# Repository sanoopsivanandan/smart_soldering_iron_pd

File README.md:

# Smart Soldering Iron (USB-C PD Powered)

A compact and affordable **USB-C PD powered smart soldering iron** designed for hobbyists and experimenters.
The project uses a **C210-style tip**, an **ATmega328P-AU**, and includes an **OLED display** and **accelerometer** for smart functions.

This repository currently contains **hardware-only KiCad files**. Firmware development will begin later.

---

## 📏 PCB Specifications

* **Size:** 15 mm × 107 mm
* **Layers:** 2-layer PCB
* **Form factor:** Ultra-slim to fit inside a pen-style soldering iron handle
* **Designed for:** C210-style soldering tip

---

## 🔌 Power System

* **Input:** USB-C Power Delivery
* **Supported Voltage:** Up to **12V** (currently limited to 12V for testing)
* **Purpose:** Drive the heater inside the C210 tip and power the MCU + peripherals

---

## 🧠 Microcontroller

* **MCU:** ATmega328P-AU
* **Package:** TQFP-32 (same package used in Arduino Uno SMD version)
* **Reason:** Easy programming, hobbyist-friendly, widely supported by Arduino IDE

---

## 🔥 Soldering Tip Support

* **Tip Type:** C210 series
* **Temperature Sensor:** Built-in thermocouple inside the tip
* **Connection:** Compact, high-current heater + thermocouple feedback

---

## 📟 Display & User Interface

* **Display:** 128×32 OLED
* **Navigation:** Buttons + planned touch navigation for PDF schematic viewing
* **Future UI Features:**

  * Temperature selection menu
  * Left-hand / right-hand screen rotation
  * Real-time tip temperature graph (optional)

---

## 🧭 Motion / Sleep Features

* **Accelerometer:** LIS3DHTR
* Planned features:

  * Auto-sleep when inactive
  * Wake-on-shake
  * Handle movement detection for safety

---

## 🧪 Project Status

| Category   | Status                        |
| ---------- | ----------------------------- |
| Hardware   | ✔ Completed (prototype ready) |
| Schematics | ✔ Completed                   |
| PCB Layout | ✔ Completed                   |
| Firmware   | ❌ Not started                 |
| Testing    | ❌ Pending                     |

---

## 🧰 Development Plans (Firmware)

Firmware will be written primarily using **Arduino IDE**, with possible low-level C enhancements.

Planned firmware features:

* PID temperature control
* USB-C PD negotiation and power step handling
* On-screen temperature display
* Menu navigation
* Accelerometer-based sleep mode
* Tip calibration

---

## 📂 Repository Structure

* `.kicad_pro` – Main KiCad project file
* `.kicad_sch` – Schematic files
* `.kicad_pcb` – PCB layout
* `pcb_front.pdf` / `pcb_back.pdf` – PDF views of the PCB
* Additional supporting schematic sheets

Touch navigation support will be added to PDF schematics to improve readability during review.

---

## 🎯 Project Goal

To create an **affordable**, **compact**, and **easily buildable** smart soldering iron that:

* Hobbyists can assemble with basic tools
* Works reliably with USB-C PD chargers
* Uses a high-quality C210 tip
* Provides a solid foundation for firmware experimentation

---

## 📜 License

No license added yet — you may add MIT / GPL / CERN OHL based on your preference.

---

## 🤝 Contributions

Contributions and suggestions are welcome once firmware development begins!

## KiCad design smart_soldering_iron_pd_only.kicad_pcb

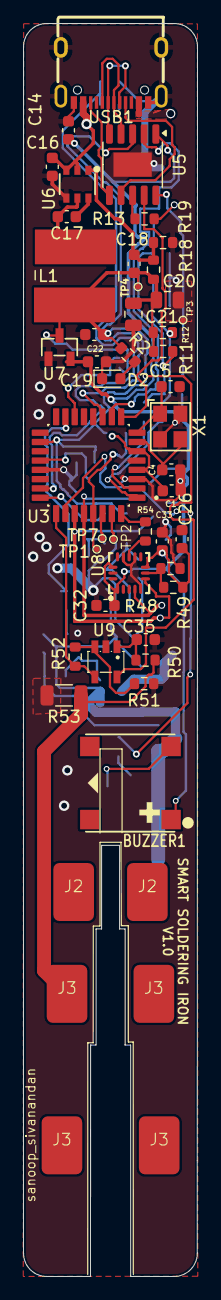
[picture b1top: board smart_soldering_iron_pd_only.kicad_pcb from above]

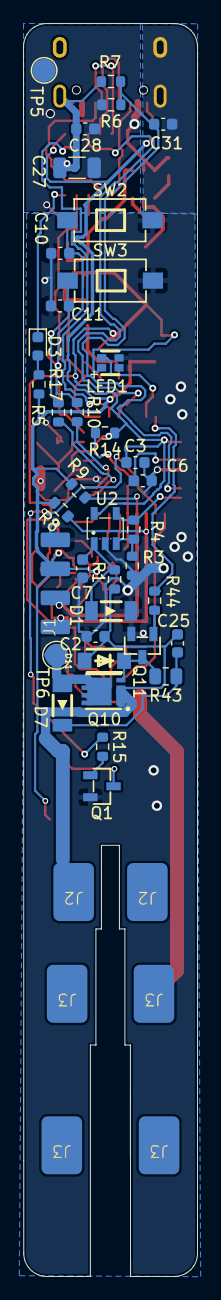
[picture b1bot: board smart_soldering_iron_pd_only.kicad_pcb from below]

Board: 2 copper layers, 15.0 x 107.9 mm, 94 parts (44 on the bottom side), 51 nets.

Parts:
BUZZER1: 2.7kHz; BUZZER_7525A_BUZ-SMD_4P-L7.5-W7.5-P7.59-TL
C1, C3, C6, C10, C11, C17, C26, C31, C32, C35: 100n; C_0603_1608Metric
C2: 1u 35V; C_0603_1608Metric
C4, C5: 22P; C_0603_1608Metric
C7: 2n2; C_0603_1608Metric
C14, C19, C22: 1u; C_0603_1608Metric
C16, C25, C33: 10u; C_0603_1608Metric
C18: 47p; C_0603_1608Metric
C20, C21: 22u; C_0805_2012Metric
C27: 100u 35V; C_1206_3216Metric
C28: 10u 35V; C_0603_1608Metric
D1, D7: D; LL4148 LL34 SOD80 1N4148 Hottech SMD diode
D2, D3: LED; LED_0603_1608Metric
D11: D_Zener; BZT52C5V1 W8_ZENER DIODE
J1: Conn_01x04_Pin; oled_display
J2, J2#2, J2#3, J2#4: TIP_SMALL_END; TIP_PADS
J3, J3#2, J3#3, J3#4, J3#5, J3#6, J3#7, J3#8: TIP_MID; TIP_PADS
L1: 4.7u; L_Wuerth_WE-PD2-Typ-L
LED1: LED-SMD_4P-L1.6-W1.5_XL-1615RGBC-WS2812B-S
Q1, Q11: S8050_TRANSIS_25V_0.5A_npn_SOT-23-3_L2.9-W1.3-P1.90-LS2.4-BR
Q10: AON7410_POWER_N_MOS_DFN-8_L3.0-W3.0-P0.65-BL
R1, R7, R8, R9, R11, R12, R13, R14, R15, R44, R48, R49: 10K; R_0603_1608Metric
R2, R3, R51, R54: 1K; R_0603_1608Metric
R4: 200K; R_0603_1608Metric
R5, R10: 0; R_0603_1608Metric
R6: 33K; R_0603_1608Metric
R17: 470; R_0603_1608Metric
R18: 9K; R_0603_1608Metric
R19: 30K; R_0603_1608Metric
R43: 1K; R_0805_2012Metric
R50: 56K; R_0603_1608Metric
R52: 75K; R_0603_1608Metric
R53: 0.01; R_1206_3216Metric
SW2, SW3: push_button_3.5x6x2.5Hmm SMD Rectangle Tactile micro Switch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
TP1, TP2, TP3, TP4, TP7: TestPoint; TestPoint_Pad_D1.5mm
TP5, TP6: TestPoint; TestPoint_Pad_D2.0mm
U2, U9: LM321_SOT-23-5_L3.0-W1.7-P0.95-LS2.8-BR
U3: ATMEGA328P-AU; ATMEGA328P-AU_QFP80P900X900X120-32N
U5: CH224K; SSOP-10-1EP_3.9x4.9mm_P1mm_EP2.1x3.3mm
U6: DIODES AP63300WU-7_buck_TSOT-23-6_L2.9-W1.6-P0.95-LS2.8-BR
U7: XC6206P332MR_SOT-23-3_L2.9-W1.3-P1.90-LS2.4-BR
U8: ST LIS3DHTR_ACCELEROMETER_LGA-16_L3.0-W3.0-P0.50-TL
USB1: USB-C-SMD_TYPE-C-6PIN-2MD-073
X1: 16MHz; 16_mhz_OSC-SMD_4P-L3.2-W2.5-BL

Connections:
<_BUTTON: R10.2, U3.2 (PD4)
>_BUTTON: R5.2, U3.1 (PD3)
AREF: C6.1, U3.20 (AREF)
BUZZER: R15.1, U3.26 (PC3)
CFG1: U3.9 (PD5), U5.9 (CFG1)
CFG2: U3.10 (PD6), U5.2 (CFG2)
CFG3: U3.11 (PD7), U5.3 (CFG3)
D0_RXD: TP1.1, U3.30 (PD0)
D1_TXD: TP2.1, U3.31 (PD1)
GND: C1.2, C2.2, C3.2, C4.2, C5.2, C6.2, C7.2, C10.1, C11.1, C14.2, C16.2, C19.2, C20.2, C21.2, C22.2, C26.1, C27.2, C28.2, C31.2, C32.1, C33.1, C35.2, D1.1 (K), D2.1 (K), J1.4, LED1.3 (GND), Q1.2 (E), Q11.2 (E), R3.1, R7.1, R19.2, R49.1, R51.1, R53.2, SW2.2, SW3.2, TP3.1, U2.2 (V-), U3.3 (GND), U3.5 (GND), U3.21 (GND), U5.11 (GND), U6.4 (GND), U7.1 (VSS), U8.5 (GND), U8.10 (RES), U8.12 (GND), U9.2 (V-), USB1.1 (GND), USB1.12 (GND), USB1.13 (SHELL), USB1.14 (SHELL), X1.2 (GND), X1.4 (GND)
LED_RGB: LED1.4 (DI), U3.14 (PB2)
LIS3DHTR_INT: R54.1, U3.32 (PD2)
unnamed: BUZZER1.2 (-), Q1.3 (C)
unnamed: C10.2, R10.1, R11.1, SW2.1
unnamed: C11.2, R5.1, R12.1, SW3.1
unnamed: C7.1, D1.2 (A), R1.2, U2.1 (IN+)
unnamed: D2.2 (A), R2.2
unnamed: D3.2 (A), R17.1
unnamed: D7.2 (A), Q10.5 (D), Q10.6 (D), Q10.7 (D), Q10.8 (D), Q10.9 (D), TP6.1
unnamed: C25.2, D7.1 (K), R43.1
unnamed: D11.1 (K), Q10.4 (G), Q11.3 (C), R43.2
unnamed: Q1.1 (B), R15.2
unnamed: Q11.1 (B), R44.2
unnamed: R3.2, R4.1, U2.3 (IN-)
unnamed: R14.2, TP7.1, U3.29 (PC6/~RESET)
unnamed: U5.7 (CC1), USB1.4 (CC1)
unnamed: U5.6 (CC2), USB1.10 (CC2)
unnamed: U5.5 (DM), USB1.5 (DN2), USB1.7 (DN1)
unnamed: U5.4 (DP), USB1.6 (DP1), USB1.8 (DP2)
unnamed: R13.2, U5.8 (VBUS)
unnamed: C17.1, U6.6 (BST)
unnamed: C18.2, R18.2, R19.1, U6.1 (FB)
unnamed: C17.2, L1.1, U6.5 (SW)
unnamed: R54.2, U8.11 (INT1)
unnamed: R48.1, R49.2, U8.7 (SDO/SA0)
unnamed: C35.1, R50.2, U9.1 (IN+)
unnamed: R51.2, R52.1, U9.3 (IN-)
PG: D3.1 (K), U5.10 (PG)
SCL: J1.2, R9.1, U3.28 (PC5), U8.4 (SCL/SPC)
SDA: J1.1, R8.1, U3.27 (PC4), U8.6 (SDA/SDI/SDO)
TEMP_SENSE: R4.2, U2.4 (OUT), U3.24 (PC1)
TIP+: C2.1, C25.1, D11.2 (A), J2#3.1, Q10.1 (S), Q10.2 (S), Q10.3 (S), R1.1
TIP-: J3#3.1, R50.1, R53.1
TIP_AMP_SENSE: R52.2, U3.25 (PC2), U9.4 (OUT)
TIP_MOS: R44.1, U3.15 (PB3)
VCC_3V3: BUZZER1.1 (+), C14.1, C19.1, C26.2, C32.2, C33.2, J1.3, R8.2, R9.2, R17.2, R48.2, U5.1 (VDD), U7.2 (VOUT), U8.1 (VDD_IO), U8.8 (CS), U8.14 (VDD)
VCC_5V: C1.1, C3.1, C18.1, C20.1, C21.1, C22.1, L1.2, LED1.2 (VDD), R2.1, R11.2, R12.2, R14.1, R18.1, TP4.1, U2.5 (V+), U3.4 (VCC), U3.6 (VCC), U3.18 (AVCC), U7.3 (VIN), U9.5 (V+)
V_SENSE: C31.1, R6.1, R7.2, U3.23 (PC0)
Vin: C16.1, C27.1, C28.1, R6.2, R13.1, TP5.1, U6.2 (EN), U6.3 (VIN), USB1.2 (VBUS), USB1.11 (VBUS)
XAL1: C4.1, U3.7 (PB6), X1.3 (OSC2)
XAL2: C5.1, U3.8 (PB7), X1.1 (OSC1)

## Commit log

2025-11-22 files uploaded
2025-11-22 test
2025-11-22 initial 1st complete version v1.0
2025-11-22 added fillet to the pcb
2025-11-23 added reset
2025-11-23 added reset test pad in atmega
2025-11-23 added name and version to the silk screen
2025-11-23 error in tip dimension,added buzzer,increased length to 11cm
2025-11-23 minor adjustment in silk screen
2025-11-23 added pdf's
2025-11-23 Add initial README for Smart Soldering Iron project
    This README provides an overview of the Smart Soldering Iron project, including specifications, power system, microcontroller details, and future development plans.
2025-11-23 added rgb led
2025-11-24 connected 5v to the tip amp measure
